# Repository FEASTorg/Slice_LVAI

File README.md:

# Low-Voltage Analog Input Reader Slice

Low-Voltage Analog Input Reader Slice for BREAD.

## Introduction

The slice reads six single-ended analog voltages into an Arduino Nano.
Each channel is the same circuit, built around one MCP6004 quad op-amp:

1. **Input divider and protection.** R2 and R4 (22 kΩ each) halve the
   terminal voltage; two BAS416 low-leakage diodes, to 5 V and to GND,
   limit the divided node in a fault (see Protection below).
2. **Offset.** A 10 kΩ trimmer sets a reference voltage, Voff (0-5 V),
   buffered by a follower.
3. **Difference stage.** With R3 = R5 = 1 kΩ it outputs Vin - Voff.
4. **Gain.** A non-inverting stage whose 10 kΩ trimmer sets
   G = 10 kΩ / R(wiper to GND), from 1 upwards.
5. **Low-pass filter.** 1 kΩ and 1 µF C0G, fc = 1 / (2π · 1 kΩ · 1 µF)
   = 159 Hz, buffered by a follower into the Nano's ADC.

The voltage at the Nano pin is G · (Vin - Voff), limited to 0-5 V by the
5 V rail. At G = 1 a channel reads a 5 V wide window of input, from Voff
to Voff + 5 V; a higher gain narrows the window.

## Inputs

- **Range:** 0-10 V, unipolar, referenced to the slice's GND (pin 2 of
  J6-J8). Bipolar inputs are planned for a later revision, see issue #2.
- **Input impedance:** 44 kΩ (R2 + R4).
- **Protection:** R2 limits the fault current. With +24 V on a terminal,
  D2 (BAS416 to 5 V) holds the divided node at about 5.75 V, 5.9 V at the
  BAS416's maximum forward voltage: inside the MCP6004's VDD + 1.0 V
  absolute maximum (Microchip DS20001733L), with 0.1 V to spare at that
  forward voltage and less in the cold. R2 then carries
  (24 - 5.75) / 22 kΩ = 0.83 mA. With -24 V the op-amp's own input diode
  conducts before D3 does and carries most of the current, 1.06 of
  1.08 mA in simulation, inside the MCP6004's ±2 mA input current limit.
  The clamps leak at most 5 nA (BAS416, 75 V, 25 °C), about 0.06 mV
  across the 11 kΩ source resistance of the divider. The clamps are
  revisited with the bipolar input (issue #2).

## Channel map

| Terminal | Channel | Nano pin | Firmware | Offset trimmer | Gain trimmer |
|---|---|---|---|---|---|
| J3 pin 1 | CH0 | A3 | `CH0(A3)` | RV1 | RV2 |
| J3 pin 2 | CH1 | A7 | `CH1(A7)` | RV3 | RV4 |
| J4 pin 1 | CH2 | A2 | `CH2(A2)` | RV5 | RV6 |
| J4 pin 2 | CH3 | A6 | `CH3(A6)` | RV7 | RV8 |
| J5 pin 1 | CH4 | A1 | `CH4(A1)` | RV9 | RV10 |
| J5 pin 2 | CH5 | A0 | `CH5(A0)` | RV11 | RV12 |

The terminals are marked CH0-CH5 on the silkscreen.

## Usage

### Setting offset and gain

Each channel has two multi-turn trimmers:

- **Offset** sets Voff = 5 V · R(wiper to GND) / 10 kΩ, the input voltage
  that reads as 0.
- **Gain** sets G = 10 kΩ / R(wiper to GND). The wiper at the top end
  gives G = 1, at 5 kΩ G = 2, at 1 kΩ G = 10. Keep it away from the GND
  end, where the stage runs open loop.

To set a channel for an input window from Vlow to Vhigh:

1. Turn the gain trimmer to G = 1.
2. Apply Vlow and turn the offset trimmer until the channel just reads
   above 0.
3. Apply Vhigh and turn the gain trimmer until the channel reads just
   below full scale (1023). G = 5 V / (Vhigh - Vlow) at most.

### Sensor supply

J6, J7 and J8 give 5 V (pin 1) and GND (pin 2) for sensors. The three
outputs share F1, a resettable fuse (Bourns MF-MSMF030): 300 mA in total
(hold current at 23 °C); it trips by 600 mA and resets once the fault
is removed. The fuse adds up to 3 Ω in series, so expect up to 0.9 V
less than 5 V at the full 300 mA. The outputs are fed from the slice's
5 V directly, not through the channels' trimmers.

### Firmware

`firmware/LVAI.ino` samples the enabled channels in the time domain
(16 samples) or runs a 64-point FFT and prints the peak frequency.

## Documentation

Please refer to the [docs](/docs) for more info.

---

<div align="center">
  
</div>

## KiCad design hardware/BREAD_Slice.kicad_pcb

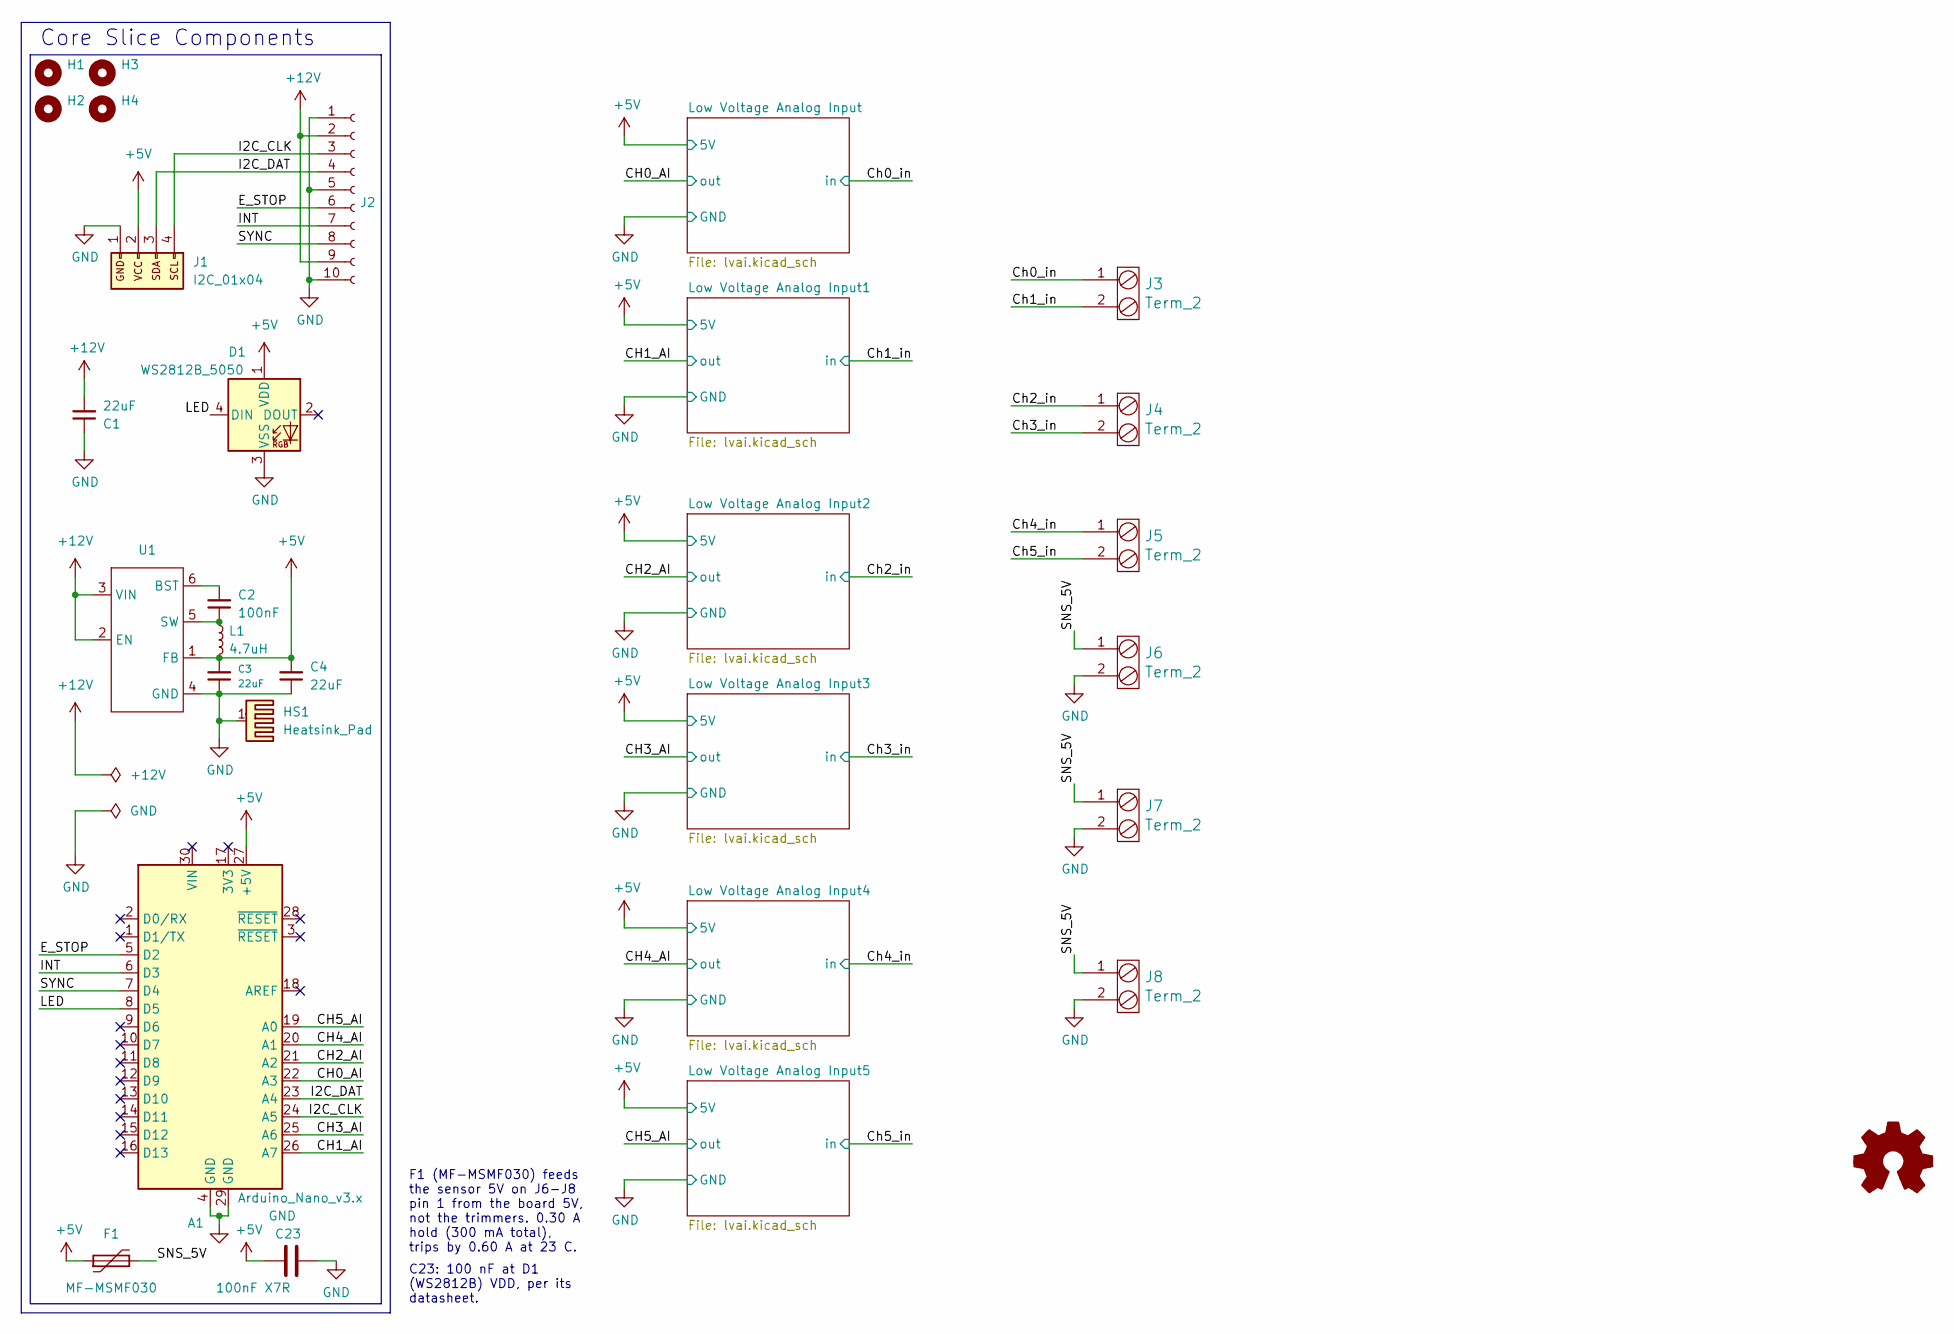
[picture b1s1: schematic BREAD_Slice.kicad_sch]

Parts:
A1: Arduino_Nano_v3.x; Arduino_Nano
C1, C3, C4: 22uF; C_1206_3216Metric
C2: 100nF; C_1206_3216Metric
C23: 100nF X7R; C_0603_1608Metric
D1: WS2812B_5050; WS2812-5050-4PIN
F1: MF-MSMF030; Fuse_1812_4532Metric
H1, H2, H3, H4: MountingHole; MountingHole_5mm
HS1: Heatsink_Pad; Thermal_Pad
J1: I2C_01x04; JST_SH_SM04B-SRSS-TB_1x04-1MP_P1.00mm_Horizontal
J2: Conn_01x10_Female; PinSocket_1x10_P2.54mm_Horizontal
J3, J4, J5, J6, J7, J8: Term_2; TerminalBlock_Phoenix_MKDS-1,5-2_1x02_P5.00mm_Horizontal; Part # 1935161
L1: 4.7uH; L_1210_3225Metric
U1: TSOT-23-6

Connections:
+5V: A1.27 (+5V), C3.2, C4.2, C23.1, D1.1 (VDD), F1.1, J1.2, L1.2, U1.1 (FB); also elsewhere on the board
+12V: C1.2, J2.2, J2.9, U1.2 (EN), U1.3 (VIN)
/CH0_AI: A1.22 (A3); also elsewhere on the board
/CH1_AI: A1.26 (A7); also elsewhere on the board
/CH2_AI: A1.21 (A2); also elsewhere on the board
/CH3_AI: A1.25 (A6); also elsewhere on the board
/CH4_AI: A1.20 (A1); also elsewhere on the board
/CH5_AI: A1.19 (A0); also elsewhere on the board
/Ch0_in: J3.1; also elsewhere on the board
/Ch1_in: J3.2; also elsewhere on the board
/Ch2_in: J4.1; also elsewhere on the board
/Ch3_in: J4.2; also elsewhere on the board
/Ch4_in: J5.1; also elsewhere on the board
/Ch5_in: J5.2; also elsewhere on the board
/E_STOP: A1.5 (D2), J2.6
/I2C_CLK: A1.24 (A5), J1.4, J2.3
/I2C_DAT: A1.23 (A4), J1.3, J2.4
/INT: A1.6 (D3), J2.7
/LED: A1.8 (D5), D1.4 (DIN)
/SNS_5V: F1.2, J6.1, J7.1, J8.1
/SYNC: A1.7 (D4), J2.8
GND: A1.4 (GND), A1.29 (GND), C1.1, C3.1, C4.1, C23.2, D1.3 (VSS), HS1.1, J1.1, J2.1, J2.5, J2.10, J6.2, J7.2, J8.2, U1.4 (GND); also elsewhere on the board
unnamed: C2.2, U1.6 (BST)
unnamed: C2.1, L1.1, U1.5 (SW)

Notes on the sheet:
Core Slice Components
F1 (MF-MSMF030) feeds the sensor 5V on J6-J8 pin 1 from the board 5V, not the trimmers. 0.30 A hold (300 mA total), trips by 0.60 A at 23 C.
C23: 100 nF at D1 (WS2812B) VDD, per its datasheet.

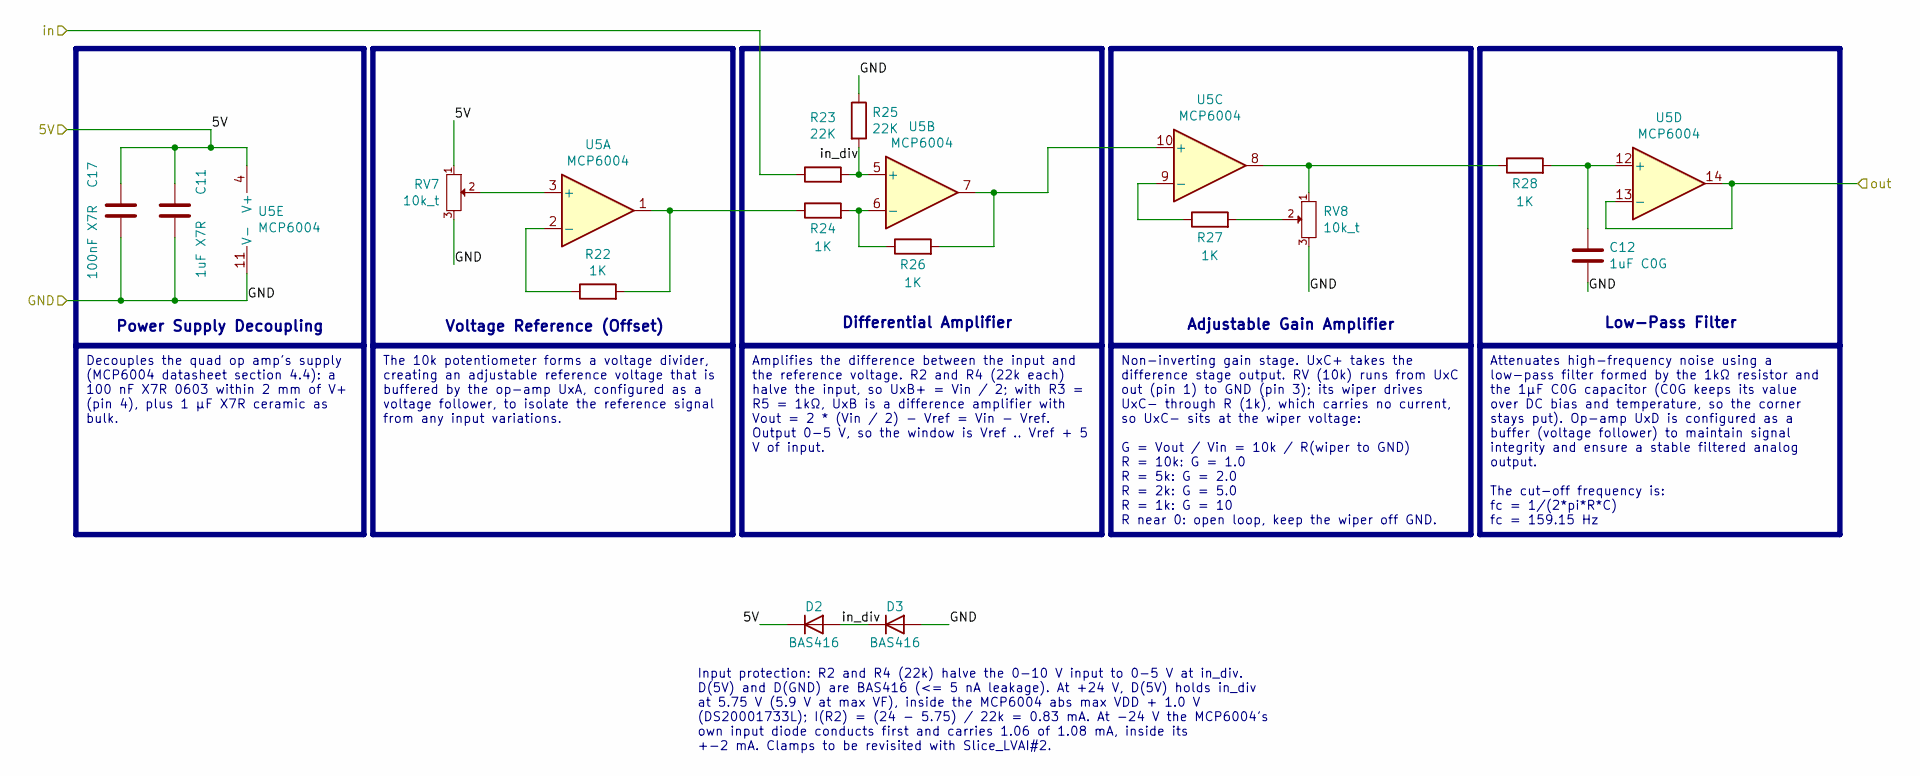
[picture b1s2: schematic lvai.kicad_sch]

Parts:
C11: 1uF X7R; C_0805_2012Metric; Part # CL21B105KAFNNNE
C12: 1uF C0G; C_1206_3216Metric_Pad1.33x1.80mm_HandSolder; Part # C3216C0G1E105J160AC
C17: 100nF X7R; C_0603_1608Metric; Part # CL10B104KB8NNNC
D2, D3: BAS416; D_SOD-323; Part # BAS416,115
R22, R24, R26, R27, R28: 1K; R_1206_3216Metric_Pad1.30x1.75mm_HandSolder; Part # RC1206FR-071KL
R23, R25: 22K; R_1206_3216Metric_Pad1.30x1.75mm_HandSolder; Part # RC1206FR-0722KL
RV7, RV8: 10k_t; Potentiometer_Bourns_3296W_Vertical; Part # 1-1623849-0
U5: MCP6004; DIP-14_W7.62mm_Socket_LongPads

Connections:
+5V: C11.1, C17.1, D2.1 (K), RV7.1, U5.4 (V+); also elsewhere on the board
/CH3_AI: U5.13 (-), U5.14; also elsewhere on the board
/Ch3_in: R23.1; also elsewhere on the board
GND: C11.2, C12.2, C17.2, D3.2 (A), R25.1, RV7.3, RV8.3, U5.11 (V-); also elsewhere on the board
unnamed: R22.2, R24.1, U5.1
unnamed: R27.2, RV8.2
unnamed: R28.1, RV8.1, U5.8
unnamed: RV7.2, U5.3 (+)
unnamed: R22.1, U5.2 (-)
unnamed: R24.2, R26.1, U5.6 (-)
unnamed: R26.2, U5.7, U5.10 (+)
unnamed: R27.1, U5.9 (-)
unnamed: C12.1, R28.2, U5.12 (+)

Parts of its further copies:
C5, C7, C9, C13, C15: 1uF X7R; C_0805_2012Metric; Part # CL21B105KAFNNNE
C6, C8, C10, C14, C16: 1uF C0G; C_1206_3216Metric_Pad1.33x1.80mm_HandSolder; Part # C3216C0G1E105J160AC
C18, C19, C20, C21, C22: 100nF X7R; C_0603_1608Metric; Part # CL10B104KB8NNNC
D4, D5, D6, D7, D8, D9, D10, D11, D12, D13: BAS416; D_SOD-323; Part # BAS416,115
R1, R3, R5, R6, R7, R8, R10, R12, R13, R14, R15, R17, R19, R20, R21, R29, R31, R33, R34, R35, R36, R38, R40, R41, R42: 1K; R_1206_3216Metric_Pad1.30x1.75mm_HandSolder; Part # RC1206FR-071KL
R2, R4, R9, R11, R16, R18, R30, R32, R37, R39: 22K; R_1206_3216Metric_Pad1.30x1.75mm_HandSolder; Part # RC1206FR-0722KL
RV1, RV2, RV3, RV4, RV5, RV6, RV9, RV10, RV11, RV12: 10k_t; Potentiometer_Bourns_3296W_Vertical; Part # 1-1623849-0
U2, U3, U4, U6, U7: MCP6004; DIP-14_W7.62mm_Socket_LongPads

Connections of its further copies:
+5V: C5.1, C7.1, C9.1, C13.1, C15.1, C18.1, C19.1, C20.1, C21.1, C22.1, D4.1 (K), D6.1 (K), D8.1 (K), D10.1 (K), D12.1 (K), RV1.1, RV3.1, RV5.1, RV9.1, RV11.1, U2.4 (V+), U3.4 (V+), U4.4 (V+), U6.4 (V+), U7.4 (V+); also elsewhere on the board
/CH0_AI: U2.13 (-), U2.14; also elsewhere on the board
/CH1_AI: U3.13 (-), U3.14; also elsewhere on the board
/CH2_AI: U4.13 (-), U4.14; also elsewhere on the board
/CH4_AI: U6.13 (-), U6.14; also elsewhere on the board
/CH5_AI: U7.13 (-), U7.14; also elsewhere on the board
/Ch0_in: R2.1; also elsewhere on the board
/Ch1_in: R9.1; also elsewhere on the board
/Ch2_in: R16.1; also elsewhere on the board
/Ch4_in: R30.1; also elsewhere on the board
/Ch5_in: R37.1; also elsewhere on the board
/Low Voltage Analog Input1/in_div: D4.2 (A), D5.1 (K), R9.2, R11.2, U3.5 (+)
/Low Voltage Analog Input2/in_div: D6.2 (A), D7.1 (K), R16.2, R18.2, U4.5 (+)
/Low Voltage Analog Input4/in_div: D10.2 (A), D11.1 (K), R30.2, R32.2, U6.5 (+)
/Low Voltage Analog Input5/in_div: D12.2 (A), D13.1 (K), R37.2, R39.2, U7.5 (+)
GND: C5.2, C6.2, C7.2, C8.2, C9.2, C10.2, C13.2, C14.2, C15.2, C16.2, C18.2, C19.2, C20.2, C21.2, C22.2, D5.2 (A), D7.2 (A), D9.2 (A), D11.2 (A), D13.2 (A), R4.1, R11.1, R18.1, R32.1, R39.1, RV1.3, RV2.3, RV3.3, RV4.3, RV5.3, RV6.3, RV9.3, RV10.3, RV11.3, RV12.3, U2.11 (V-), U3.11 (V-), U4.11 (V-), U6.11 (V-), U7.11 (V-); also elsewhere on the board
unnamed: R1.2, R3.1, U2.1
unnamed: R6.2, RV2.2
unnamed: R7.1, RV2.1, U2.8
unnamed: R8.2, R10.1, U3.1
unnamed: R13.2, RV4.2
unnamed: R14.1, RV4.1, U3.8
unnamed: R15.2, R17.1, U4.1
unnamed: R20.2, RV6.2
unnamed: R21.1, RV6.1, U4.8
unnamed: R29.2, R31.1, U6.1
unnamed: R34.2, RV10.2
unnamed: R35.1, RV10.1, U6.8
unnamed: R36.2, R38.1, U7.1
unnamed: R41.2, RV12.2
unnamed: R42.1, RV12.1, U7.8
unnamed: RV1.2, U2.3 (+)
unnamed: R1.1, U2.2 (-)
unnamed: R3.2, R5.1, U2.6 (-)
unnamed: R5.2, U2.7, U2.10 (+)
unnamed: R6.1, U2.9 (-)
unnamed: C6.1, R7.2, U2.12 (+)
unnamed: RV3.2, U3.3 (+)
unnamed: R8.1, U3.2 (-)
unnamed: R10.2, R12.1, U3.6 (-)
unnamed: R12.2, U3.7, U3.10 (+)
unnamed: R13.1, U3.9 (-)
unnamed: C8.1, R14.2, U3.12 (+)
unnamed: RV5.2, U4.3 (+)
unnamed: R15.1, U4.2 (-)
unnamed: R17.2, R19.1, U4.6 (-)
unnamed: R19.2, U4.7, U4.10 (+)
unnamed: R20.1, U4.9 (-)
unnamed: C10.1, R21.2, U4.12 (+)
unnamed: RV9.2, U6.3 (+)
unnamed: R29.1, U6.2 (-)
unnamed: R31.2, R33.1, U6.6 (-)
unnamed: R33.2, U6.7, U6.10 (+)
unnamed: R34.1, U6.9 (-)
unnamed: C14.1, R35.2, U6.12 (+)
unnamed: RV11.2, U7.3 (+)
unnamed: R36.1, U7.2 (-)
unnamed: R38.2, R40.1, U7.6 (-)
unnamed: R40.2, U7.7, U7.10 (+)
unnamed: R41.1, U7.9 (-)
unnamed: C16.1, R42.2, U7.12 (+)

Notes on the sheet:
Voltage Reference (Offset)
Differential Amplifier
Power Supply Decoupling
Low-Pass Filter
Adjustable Gain Amplifier
The 10k potentiometer forms a voltage divider, creating an adjustable reference voltage that is buffered by the op-amp UxA, configured as a voltage follower, to isolate the reference signal from any input variations.
Non-inverting gain stage. UxC+ takes the difference stage output. RV (10k) runs from UxC out (pin 1) to GND (pin 3); its wiper drives UxC- through R (1k), which carries no current, so UxC- sits at the wiper voltage: G = Vout / Vin = 10k / R(wiper to GND) R = 10k: G = 1.0 R = 5k: G = 2.0 R = 2k: G =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
Decouples the quad op amp's supply (MCP6004 datasheet section 4.4): a 100 nF X7R 0603 within 2 mm of V+ (pin 4), plus 1 µF X7R ceramic as bulk.
Attenuates high-frequency noise using a low-pass filter formed by the 1kΩ resistor and the 1μF C0G capacitor (C0G keeps its value over DC bias and temperature, so the corner stays put). Op-amp UxD is configured as a buffer (voltage follower) to maintain signal integrity and ensure a stable filtered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
Amplifies the difference between the input and the reference voltage. R2 and R4 (22k each) halve the input, so UxB+ = Vin / 2; with R3 = R5 = 1kΩ, UxB is a difference amplifier with Vout = 2 * (Vin / 2) - Vref = Vin - Vref. Output 0-5 V, so the window is Vref .. Vref + 5 V of input.
Input protection: R2 and R4 (22k) halve the 0-10 V input to 0-5 V at in_div. D(5V) and D(GND) are BAS416 (<= 5 nA leakage). At +24 V, D(5V) holds in_div at 5.75 V (5.9 V at max VF), inside the MCP6004 abs max VDD + 1.0 V (DS20001733L); I(R2) = (24 - 5.75) / 22k = 0.83 mA. At -24 V the MCP6004's own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

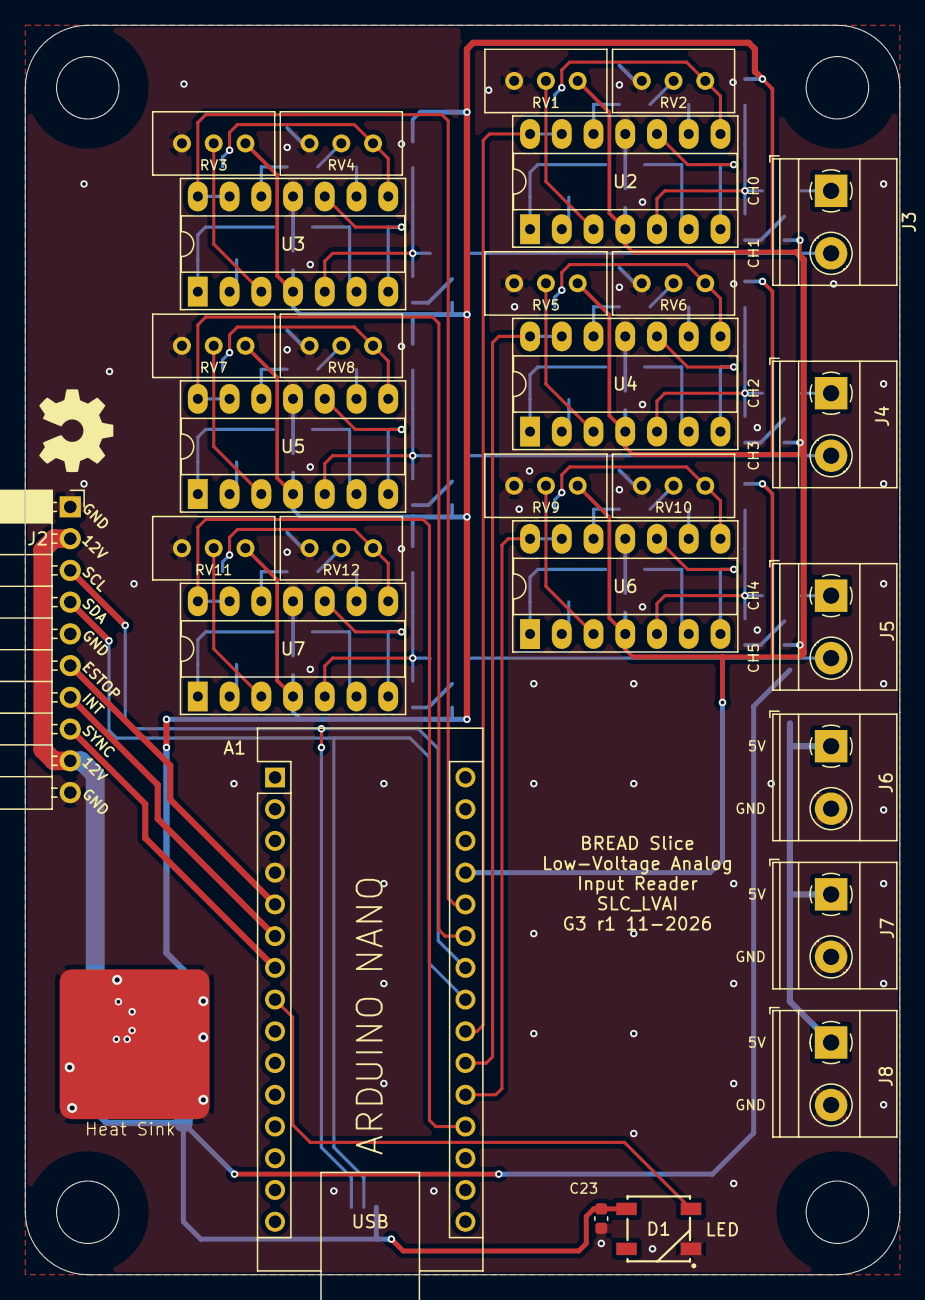
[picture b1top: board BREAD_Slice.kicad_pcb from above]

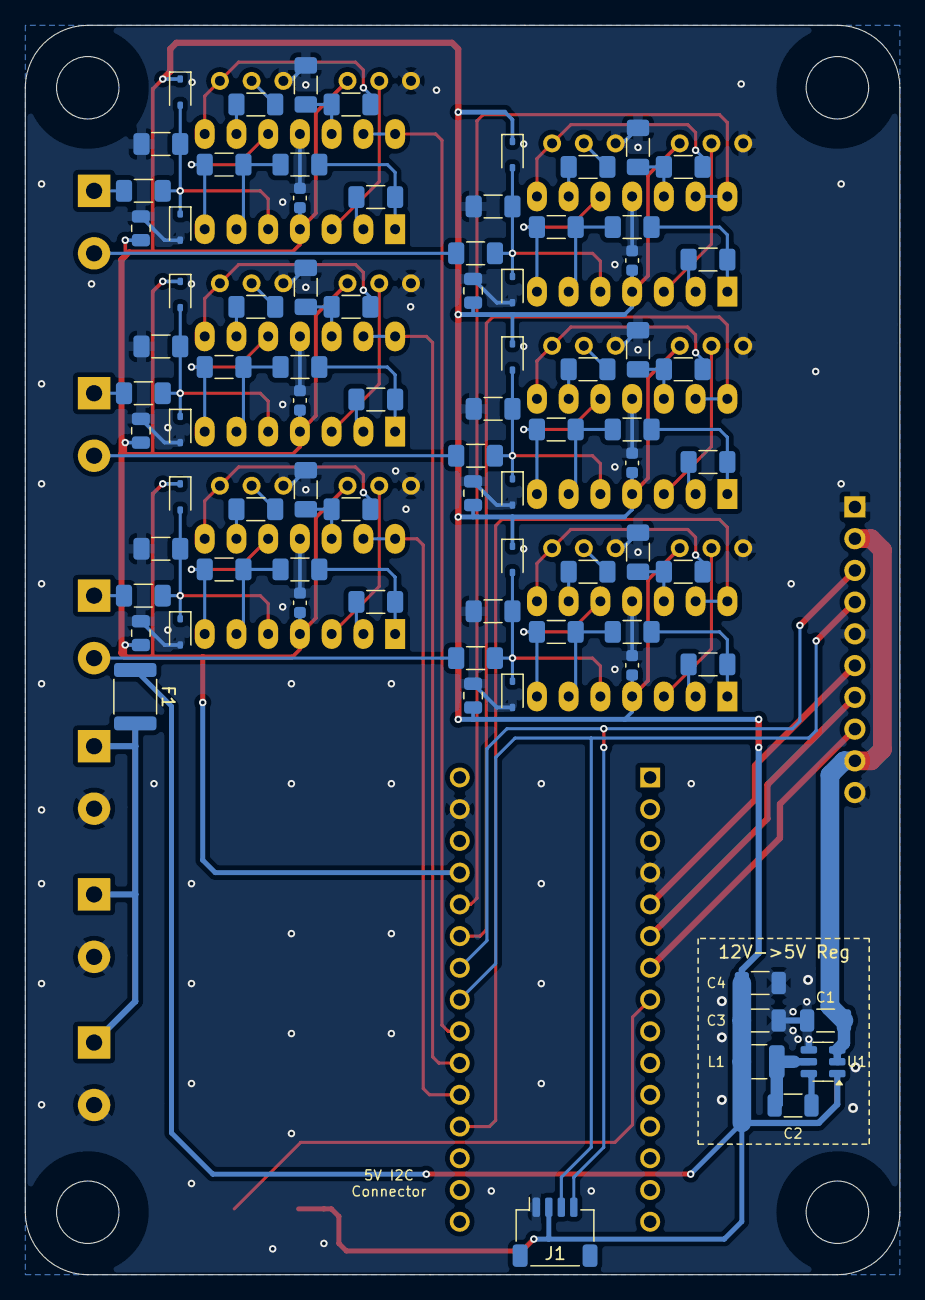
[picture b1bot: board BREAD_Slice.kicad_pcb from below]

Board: 2 copper layers, 70.0 x 100.0 mm, 114 parts (80 on the bottom side), 84 nets.

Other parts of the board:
Logo1: Logo_Open_Hardware_Small; OSHW-Symbol_6.7x6mm_SilkScreen

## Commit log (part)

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2024-09-10 set repo
2024-09-12 extensive documentation, remade board, subcircuits for all
2024-09-30 JLCPCB order rev-A
2026-04-18 chore: minor updates
2026-05-20 Add slice.yaml manifest (schema v1.0)
2026-05-24 Add KiBot/docs pipeline
2026-05-24 📄 KiBot index + board renders (auto)
2026-05-24 TODO: all CI green
2026-05-24 Standardize TODO.md with Pass 1/Pass 2 structure
